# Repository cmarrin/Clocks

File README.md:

# Clocks
Various clock hardware code

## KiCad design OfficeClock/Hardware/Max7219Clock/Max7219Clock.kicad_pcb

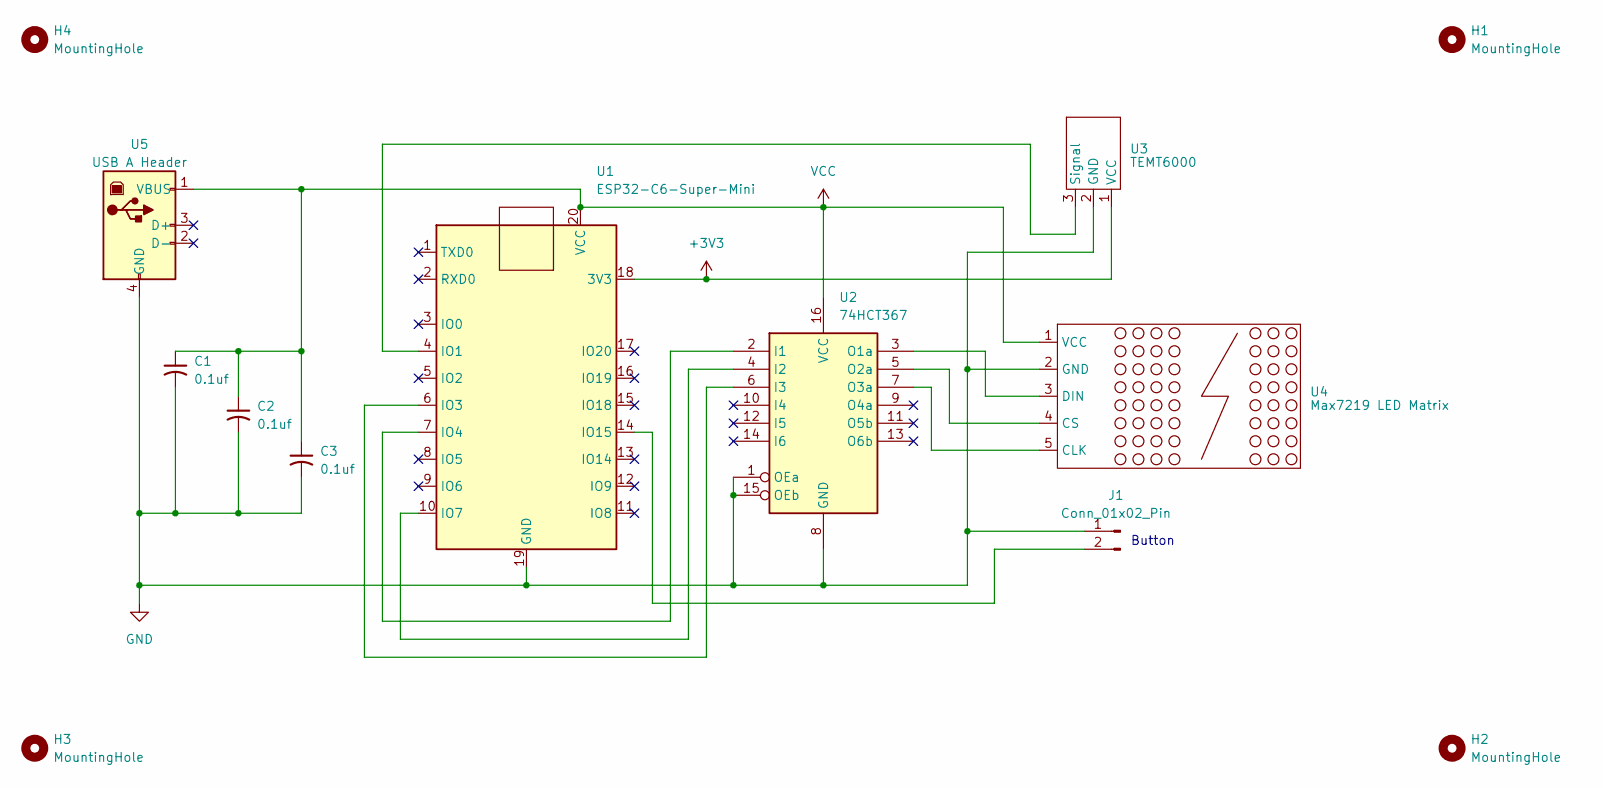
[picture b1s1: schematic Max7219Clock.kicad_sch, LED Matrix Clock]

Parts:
C1, C2, C3: 0.1uf; C_Disc_D8.0mm_W5.0mm_P5.00mm
H1, H2, H3, H4: MountingHole; MountingHole_2.2mm_M2
J1: Conn_01x02_Pin; PinHeader_1x02_P2.54mm_Vertical
U1: ESP32-C6-Super-Mini; ESP32-C6-SuperMini
U2: 74HCT367; DIP-16_W7.62mm_Socket
U3: TEMT6000; PinHeader_1x03_P2.54mm_Vertical
U4: Max7219 LED Matrix; PinSocket_1x05_P2.54mm_Horizontal
U5: USB A Header; PinHeader_1x04_P2.54mm_Vertical

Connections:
+3V3: U1.18 (3V3), U3.1 (VCC)
GND: C1.2, C2.2, C3.2, J1.1, U1.19 (GND), U2.1 (OEa), U2.8 (GND), U2.15 (OEb), U3.2 (GND), U4.2 (GND), U5.4 (GND)
unnamed: J1.2, U1.14 (IO15)
unnamed: U1.4 (IO1), U3.3 (Signal)
unnamed: U1.6 (IO3), U2.6 (I3)
unnamed: U1.7 (IO4), U2.2 (I1)
unnamed: U1.10 (IO7), U2.4 (I2)
unnamed: U2.3 (O1a), U4.3 (DIN)
unnamed: U2.5 (O2a), U4.4 (CS)
unnamed: U2.7 (O3a), U4.5 (CLK)
VCC: C1.1, C2.1, C3.1, U1.20 (VCC), U2.16 (VCC), U4.1 (VCC), U5.1 (VBUS)

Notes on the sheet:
Button

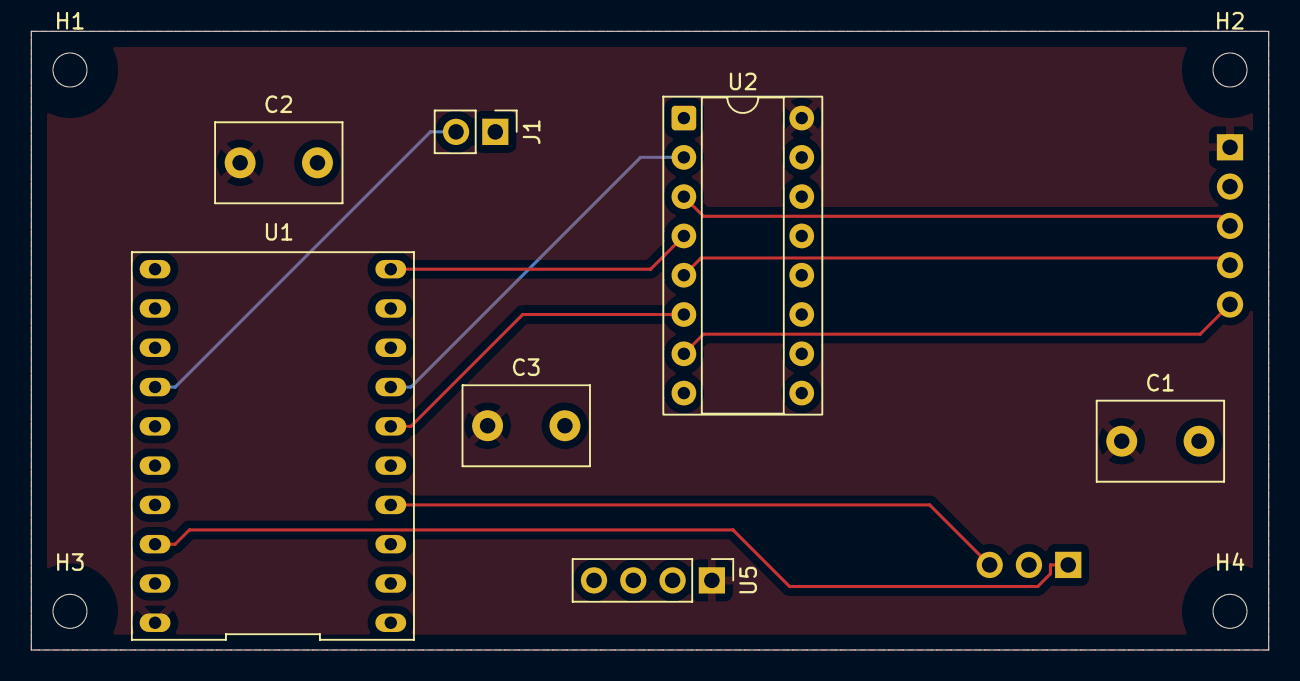
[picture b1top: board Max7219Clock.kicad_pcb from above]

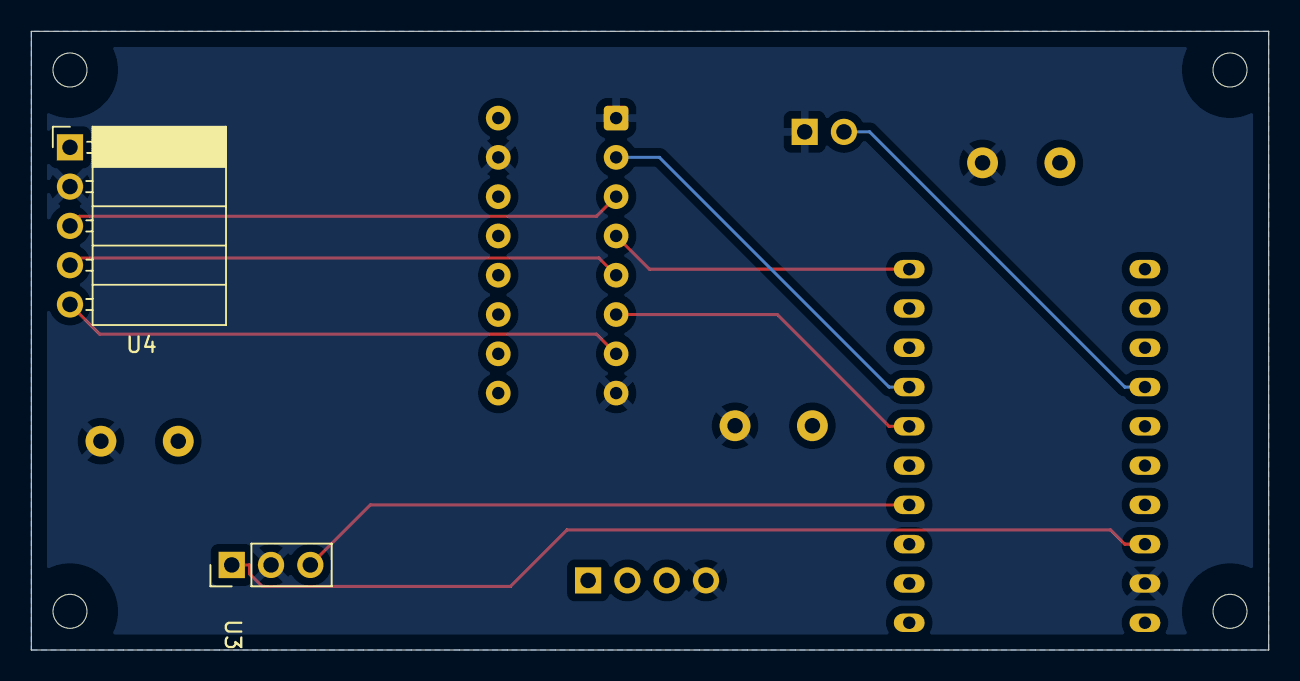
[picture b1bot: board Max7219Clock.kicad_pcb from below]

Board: 2 copper layers, 80.0 x 40.0 mm, 13 parts (2 on the bottom side), 11 nets.

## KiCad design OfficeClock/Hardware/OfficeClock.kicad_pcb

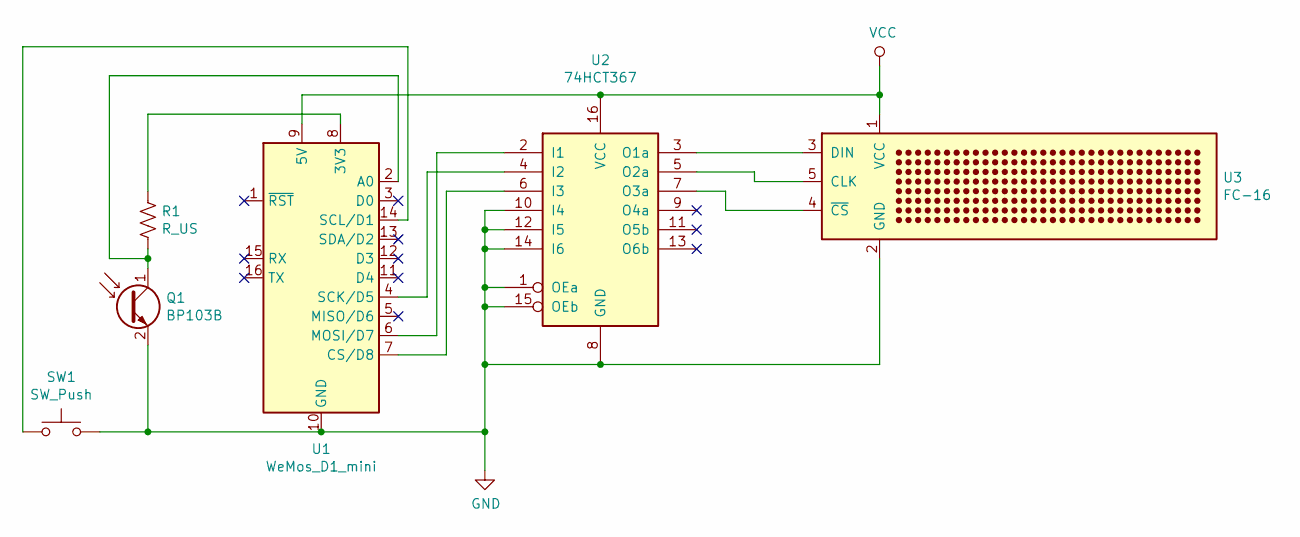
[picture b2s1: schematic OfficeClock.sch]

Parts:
Q1: BP103B; PhotoTransistor_Osram_LPT80A
R1: R_US; R_Axial_DIN0207_L6.3mm_D2.5mm_P10.16mm_Horizontal
SW1: SW_Push; Push_E-Switch_KS01Q01
U1: WeMos_D1_mini; D1-MINI
U2: 74HCT367; DIP-16_W10.16mm_LongPads
U3: FC-16; FC-16-Short

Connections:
GND: Q1.2 (E), SW1.2, U1.10 (GND), U2.1 (OEa), U2.8 (GND), U2.10 (I4), U2.12 (I5), U2.14 (I6), U2.15 (OEb), U3.2 (GND)
unnamed: Q1.1 (C), R1.2, U1.2 (A0)
unnamed: R1.1, U1.8 (3V3)
unnamed: SW1.1, U1.14 (SCL/D1)
unnamed: U1.4 (SCK/D5), U2.4 (I2)
unnamed: U1.6 (MOSI/D7), U2.2 (I1)
unnamed: U1.7 (CS/D8), U2.6 (I3)
unnamed: U2.3 (O1a), U3.3 (DIN)
unnamed: U2.5 (O2a), U3.5 (CLK)
unnamed: U2.7 (O3a), U3.4 (~CS)
VCC: U1.9 (5V), U2.16 (VCC), U3.1 (VCC)

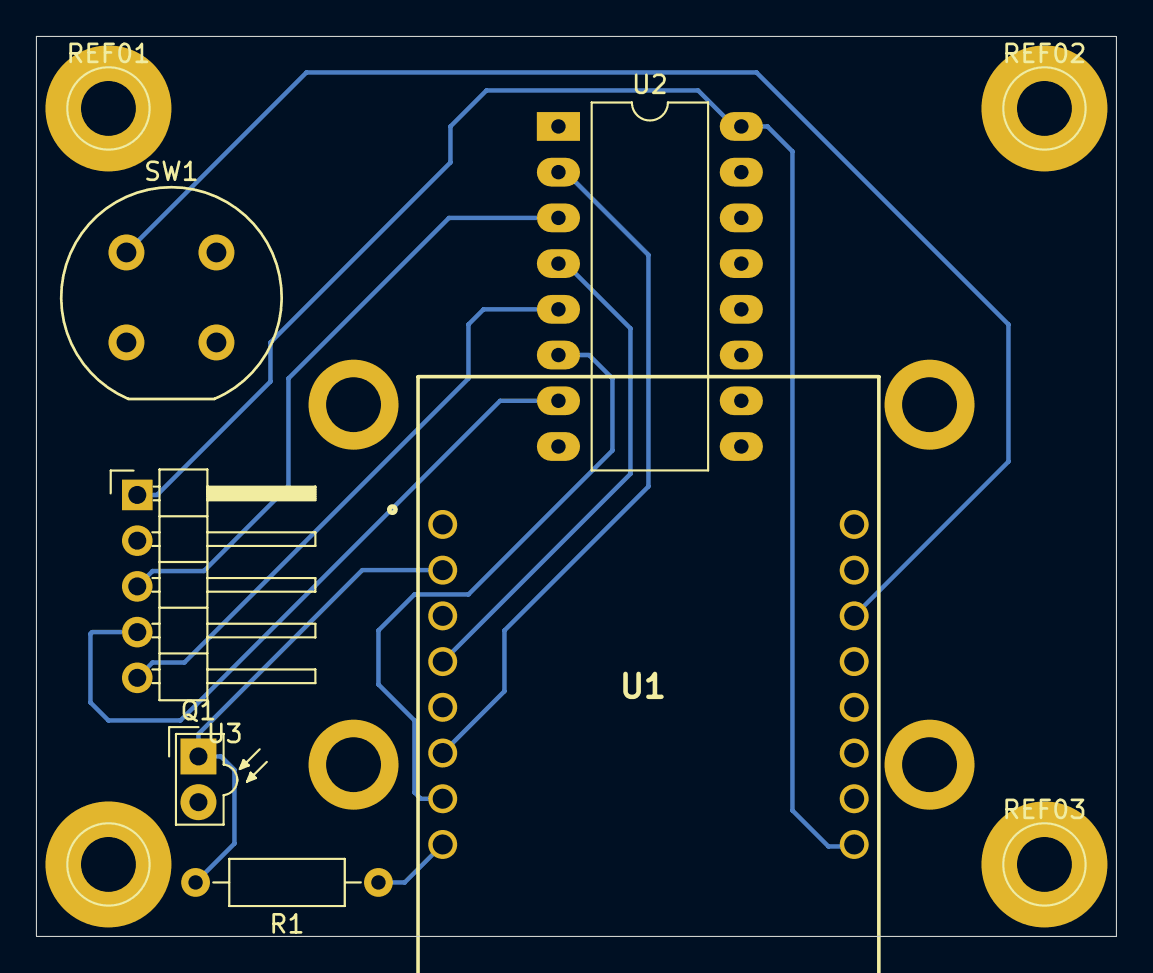
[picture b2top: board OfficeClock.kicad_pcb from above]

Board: 2 copper layers, 60.0 x 50.0 mm, 10 parts (0 on the bottom side), 11 nets.

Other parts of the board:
REF01, REF02, REF03, REF04: 1pin

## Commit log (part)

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2018-03-24 Initial checkin.
    OfficeClock.ino works with custom font. Uses 8 x 32 matrix LED module from eBay, based on 4 MAX7219s
2018-03-25 Reformatted ino file to make it pretty
2018-03-26 Updated font, mostly so it can display a "Failed" message
2018-03-26 Added small characters to spell the word "connect" on startup
2018-03-26 Moved BrightnessManager to a separate file in the m8r library
2018-03-26 Code Cleanup
2018-03-27 Moved everything into a class
    The only global is now the OfficeClock instance. Everything is cleaned up now
2018-03-31 Start using ROMStrings everywhere.
    Saved about 1400 RAM bytes
2018-03-31 Moved body of ClockDisplay functions to cpp file
2018-04-01 Revert "Added small characters to spell the word "connect" on startup"
    This reverts commit 263efecee98422f672e8d0760da1024822a74a27.
2018-04-01 Added compact font and setFont support to ClockDisplay
    I also changed the names to be more generic
2018-04-01 Got rid of special characters in normal font and start using compact font for "connect" message
2018-04-01 Improved look of lower case characters
    Made them more uniform in height
2018-04-01 Switch Menu system to use compact font
2018-04-01 Moved ClockDisplay to m8r library
    Renamed it to Max7219 display
2018-04-02 Changed ButtonManager to pass lambda as its handler callback
2018-04-03 Reenabled temp display and sped up the scroll
2018-04-03 Changed WUnderground callback to lambda passed to ctor
2018-04-03 Made callback to MenuSystem a lambda to the ctor
2018-04-04 Changed scrollDone callback of Max7219Display to be a lambda
2018-04-04 Did some cleanup and got rid of unused code
2018-04-05 Sped up info display scrolling
2018-04-05 Improvements to state machine logic
    Now you can go into setup and get out with a long press. Also now time always
    displays after a scroll
2018-04-06 Renamed setString and setTime to make them more clear
2018-04-07 Change "Setup?" string to use the full size string
    It now uses the Watusi mode of Max7219Display to let you see the whole thing
2018-04-07 change connecting message to use compact font and to Watusi rather than scroll
2018-04-07 Got rid of cancelConfigPortal
    This was from my fork of WiFiManager which I'm no longer using
2018-04-07 Use new string value in StateMachine
    Used to display "Setup?" in setup state
2018-04-07 Switched to using new Max7219Display::showString with control characters
2018-04-07 Added next and back buttons
2018-04-08 Improved network reset logic
    You can now have the network come up normally then do the reset network
    UI and it goes into config mode. You connect to the config portal, enter credentials
    and everything starts back up with the new network settings and successfully connects
2018-04-08 Got rid of debug prints
2018-04-08 Add a breakout function
    Now LongPress is set as the common next state for the state machine
    No matter what state you're in, doing a LongPress will enter setup
2018-04-08 Code cleanup and optimization
    - Made all states that just output a string use the String variant of addState
    - Put all strings in PROGMEM
2018-04-08 WIP - adjust hours in settings
    You can now go Setup->Time/date->Select and time with hours underscored will show.
    Pressing Next will advance the hour. If you then go Back twice you'll see the updated
    time. But that's all that's implemented and the next time it looks up the time from the
    network it will change back
2018-04-09 Added print of wifi mode when starting up
2018-04-09 Added setting for minutes and AM/PM
2018-04-10 Added saving of setting time
    Once you've changed a value in settingTime it asks you if you want to
    save time whenever you hit back. Hitting select will disable the network
    time setting and use the settingTime as the currentTime. In this mode
    weather is not displayed in info
2019-03-08 Added file for Etherclock, ESP based clock with DSP-7S04B display
2019-03-09 Updated Etherclock to later m8r library
    Uses StateMachine to display date (short press) and countdown timer (long press followed by another long press).
2019-03-13 Added comment indicating which board to use in the IDE
2019-03-13 Added comment with more details about OfficeClock hardware
2019-03-15 Added support for WeatherServer
2019-03-15 Updated comment
2019-03-22 Changed the brightness controls for the new light sensor board
2019-04-04 Added graphics for WordClock overlay
2019-04-04 Changed messages from bounce to scroll
2019-05-28 Updated docs for OfficeClock
2019-05-28 Updated keys for OfficeClock
2019-05-28 Finalized state machine for Office Clock.
    Now a long press asks to restart. Another long press restarts. A short press asks to reset network. Another long press asks if you're sure. Another long press does the reset.
2019-05-28 Added Kicad files for OfficeClock PCB
2021-12-03 Added file with text for WordClock
2021-12-03 Moved and renamed WordClock text file
2021-12-03 Updated refs to new mil library
2021-12-04 Got rid of unneeded print from driver
2021-12-04 Made EtherClock work as a subclass of Clock
2021-12-04 Made OfficeClock a subclass of Clock
2022-04-03 Got rid of custom ROMString handling. Just use Arduino
2022-04-03 Increased delay and added newlines at beginning to make debug messages stand out
2022-04-04 Added more fonts
2022-04-05 Updated EtherClock to new API
2022-04-05 Added ESPLib as a submodule
2022-04-05 Have clocks pass params for BrightnessManager
2022-04-09 Have WordClock display some sample time and connection info.
2022-04-11 Got time and weather showing
    WordBoard class is where all the action is. For now the test simply sends the current minute since midnight to setTime and it shows the time. The test increments the times 5 times a second. A static 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
2022-04-11 Fixed some bugs causing the wrong time to display and made the corner come on additively rather than one at a time
2022-04-14 Updated Affinity file
2022-04-14 Added Affinity file with WordClock array in Pesta Stencil
2024-02-01 Updated ESPLib
2024-02-01 Changed BrightnessManager to pass light sensor levels
2024-02-01 Fiddled where stuff goes in Project file
2024-02-01 Added ino file for WordClock
2024-02-01 Add some ignores
2024-02-10 Fixed which port button is on for OfficeClock
2024-02-10 Brought OfficeClock up to new BrightnessManager design
2024-02-13 Added Scheme for WordClock
2024-03-26 Update submodule
2024-03-26 Update ESPLib
2024-11-20 Added GL_SILENCE_DEPRECATION to silence GL warnings
2024-11-20 More GL_SILENCE_DEPRECATION stuff
2024-11-20 Added tigr as a submodule
2024-11-20 Updated to recommended settings
2024-11-20 Added tigr as a submodule again
2024-11-21 Moved WordClock from ESPLib to here
2024-11-21 Added back in dummy main for EtherClock
2024-11-21 Cleaned up mac simulator of WordClock
2024-11-21 update tigr repo
2024-11-21 Update tigr
2024-11-22 Got rid of extraneous prints
2024-11-22 Moved Application to the right place
2024-11-23 Implemented Etherclock running on Mac.
    Still many errors, but it builds and runs
2024-11-23 Got Etherclock ticking correctly on Mac
    Still doesn't show correct time because it's not being fetched. But it changed every minute like it should
2024-11-24 Moved Etherclock class to its own file so I can share it between ESP and Mac
2024-11-24 Got unified Etherclock class working for Mac
2024-11-24 Got Etherclock working mostly on ESP9266
    No colon and button doesn't work
2024-11-24 Add LightSensor to EtherClock
2024-11-24 Changed colon setting to happen before print so it turns on or off when print is called. And setDot after print so it doesn't get erased
2024-11-25 Got OfficeClock working
2024-11-25 Changed all uses of gmtime to gmtime_r which uses its own buffer
2024-11-27 Moved ButtonManager and BrightnessManager into Etherclock and OfficeClock
2024-11-27 Moved includes for BrightnessManager and ButtonManager to Etherclock and OfficeClock
2025-01-05 Pass true for send input when it happens in a separate thread.
    This avoids the race condition
2025-01-06 Got brightness working better on OfficeClock
2025-05-27 no message
2025-05-30 Support ZipCode in web server
2025-05-30 Add Format library
    Not using it yet
2025-05-30 Added Format.h header
2025-05-30 Got rid of setBrightness in setup
    It's already being set before this and this was just making it have a bright flash on startup
2025-06-07 Fixed indentation
2025-06-07 Cleaned up OfficeClock code and moved methods from .h to .cpp
2025-06-11 Got rid of passed hostname on EtherClock
2025-06-11 Got rid of Format
2025-06-11 Got rid of HTTP handler testing
    It's in PostLightController now
2025-06-11 Fixed indent
2025-08-19 Update to C++20
2025-08-19 Updates for newer version of wrapped String class
2026-03-09 Ignore some stuff
2026-03-09 Added the beginnings of an OfficeClock project for espidf
2026-03-12 Updated OfficeClock on Mac to use tigr to render the display in a window.
2026-03-12 WIP - Trying to get OfficeClock working in espidf.
    Not building yet
2026-03-12 Moved OfficeClock instance inside main so it doesn't init too early on espidf
2026-03-12 Added a partitions.csv so we can make the app partitions big enough
2026-03-12 Added sdkconfig to source control
2026-03-13 Got rid of duplicated Clock instance
2026-03-13 Turned off invert of ambient light level for now so display doesn't start out super bright
2026-03-13 Updated sdkconfig for ESP32-C6 support
2026-03-13 Updating sdkconfig
2026-03-13 Added sdkconfig.defaults to override sdkconfig settings
    This is for the 16mb part. I'll do another for the 4mb parts
2026-03-14 Restored Invert for ADC
2026-03-21 Changed name of HTTPClient to HTTPFetchClient
2026-03-22 Changed range of brightness for OfficeClock
2026-03-22 Added Kconfig.projbuild to OfficeClock
    Should probably add config settings for ClockDisplay SPI pins and Select button pin. For now it's just for the LED
2026-03-22 Adjusted stack sizes
2026-03-29 Invert the sense of the select button in tigr
2026-03-31 Added activeHigh param to OfficeClock for button
    This allows me to make the button work on both idf and Mac
2026-03-31 One more file for activeHigh fix
2026-03-31 Added documentation for switching Office Clock from ESB8266 D1 Mini to ESP32C6 Super Mini
2026-04-04 Moved select button to GPIO 18
2026-04-04 Added config for ESP32c3 and got defaults to be included correctly
    sdkconfig.defaults doesn't get included unless you add it to the project_configuration. I also moved the 4mb an 16mb defaults files to simpler names to avoid confusion
2026-04-12 Got rid of Etherclock.ino
2026-04-12 Ignore stuff
2026-04-12 Added some prints to Etherclock
2026-04-12 Got Mac Etherclock working (sort of)
    Mac now attempts to simulate the DSP7S04B. Digits are all positioned wrong, but it's getting there
2026-04-13 Fixed LED segment positions
    Now Mac displays simulated clock correctly including date and weather
2026-04-13 Added day of the week to info display
2026-04-20 Fixed documentation for where light sensor input is
2026-04-20 Made CMakeLists nicer format
2026-04-20 Getting rid of cruft
